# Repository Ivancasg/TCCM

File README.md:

# TCCM
Tarjeta de control para cámara de maduración

Desarrollado por alumnos del ITM (Instituto tecnológico de Mérida)

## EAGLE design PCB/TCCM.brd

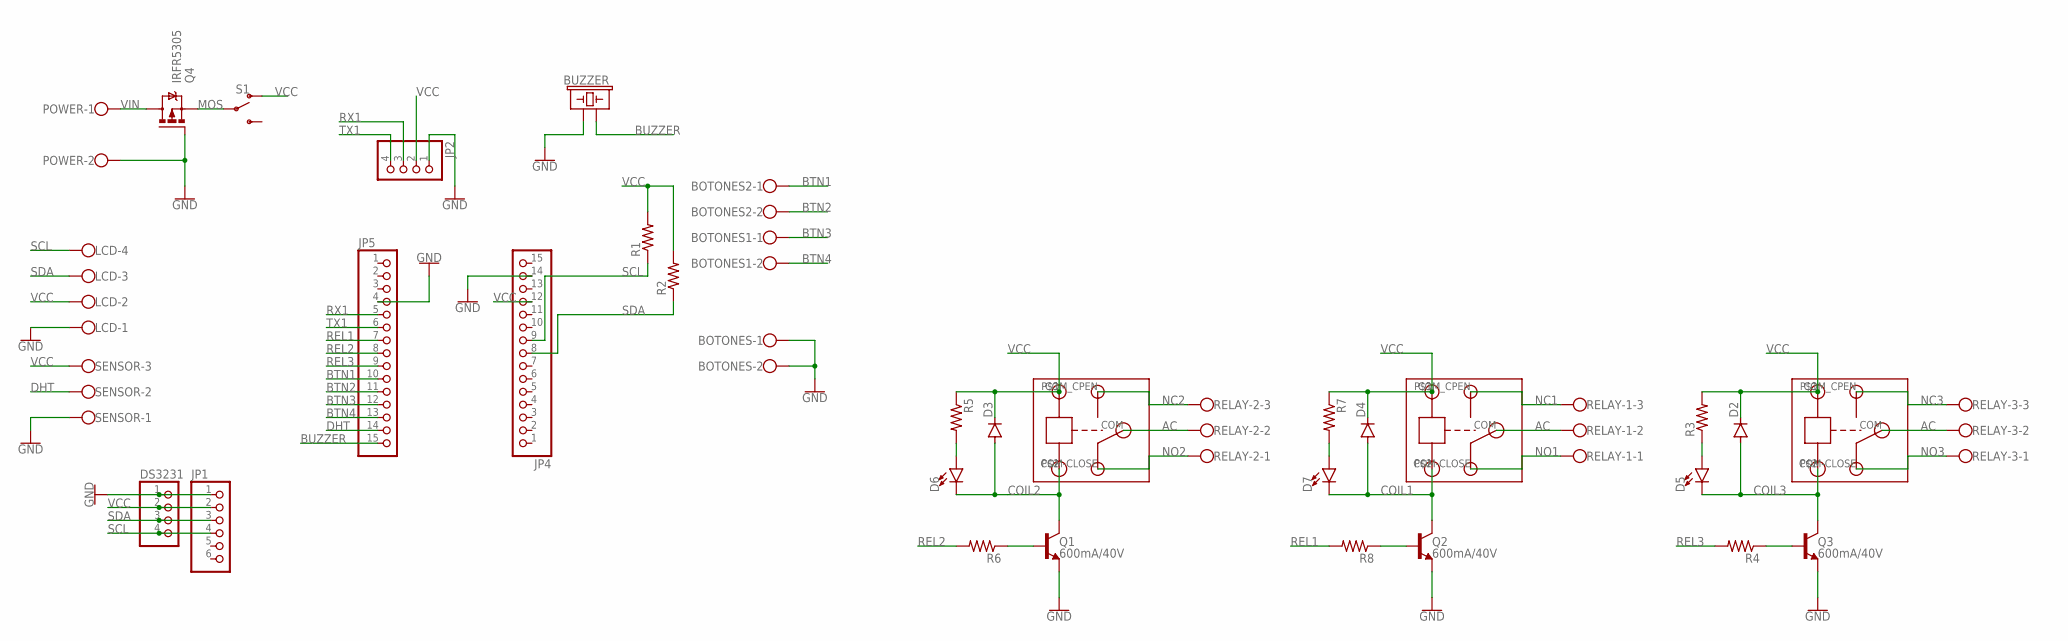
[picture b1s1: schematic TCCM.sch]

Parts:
BOTONES, BOTONES1, BOTONES2: W237-102
BUZZER: BUZZER-PTH; BUZZER-12MM
D2, D3, D4: 1N4148DO35-7; DO35-7
D5, D6, D7: LED3MM; LED_3MM
DS3231: PINHD-1X4; 1X04
JP1: PINHD-1X6; 1X06
JP2: PINHD-1X4; 1X04
JP4, JP5: PINHD-1X15; 1X15
LCD: W237-4
POWER: W237-102
Q1, Q2, Q3: 600mA/40V; TO-92
Q4: IRFR5305; D-PAK_TO252AA
R1, R2, R3, R4, R5, R6, R7, R8: R-US_0207/7; 0207/7
RELAY-1, RELAY-2, RELAY-3: W237-103
S1: SWITCH-SPDT-PTH-11.6X4.0MM; SWITCH_SPDT_PTH_11.6X4.0MM
SENSOR: W237-103
U$1, U$2, U$3: RELAY

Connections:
AC: RELAY-1.2, RELAY-2.2, RELAY-3.2, U$1.COM, U$2.COM, U$3.COM
BTN1: BOTONES2.1, JP5.10
BTN2: BOTONES2.2, JP5.11
BTN3: BOTONES1.1, JP5.12
BTN4: BOTONES1.2, JP5.13
BUZZER: BUZZER.+ (1), JP5.15
COIL1: D4.A, D7.K (C), Q2.1 (C), U$2.P$2 (GND)
COIL2: D3.A, D6.K (C), Q1.1 (C), U$1.P$2 (GND)
COIL3: D2.A, D5.K (C), Q3.1 (C), U$3.P$2 (GND)
DHT: JP5.14, SENSOR.2
GND: BOTONES.1, BOTONES.2, BUZZER.- (2), DS3231.1, JP1.1, JP2.1, JP4.14, JP5.4, LCD.1, POWER.2, Q1.3 (E), Q2.3 (E), Q3.3 (E), Q4.1 (G), SENSOR.1
LED1: D7.A, R7.2
LED2: D6.A, R5.2
LED3: D5.A, R3.1
MOS: Q4.3 (S), S1.2
unnamed: Q3.2 (B), R4.1
unnamed: Q2.2 (B), R8.1
unnamed: Q1.2 (B), R6.1
NC1: RELAY-1.3, U$2.COM_CPEN (COM-OPEN)
NC2: RELAY-2.3, U$1.COM_CPEN (COM-OPEN)
NC3: RELAY-3.3, U$3.COM_CPEN (COM-OPEN)
NO1: RELAY-1.1, U$2.COM-CLOSE
NO2: RELAY-2.1, U$1.COM-CLOSE
NO3: RELAY-3.1, U$3.COM-CLOSE
REL1: JP5.7, R8.2
REL2: JP5.8, R6.2
REL3: JP5.9, R4.2
RX1: JP2.3, JP5.5
SCL: DS3231.4, JP1.4, JP4.9, LCD.4, R1.1
SDA: DS3231.3, JP1.3, JP4.8, LCD.3, R2.1
TX1: JP2.4, JP5.6
VCC: D2.C, D3.C, D4.C, DS3231.2, JP1.2, JP2.2, JP4.12, LCD.2, R1.2, R2.2, R3.2, R5.1, R7.1, S1.1 (O), SENSOR.3, U$1.P$1 (IN), U$2.P$1 (IN), U$3.P$1 (IN)
VIN: POWER.1, Q4.4 (D)

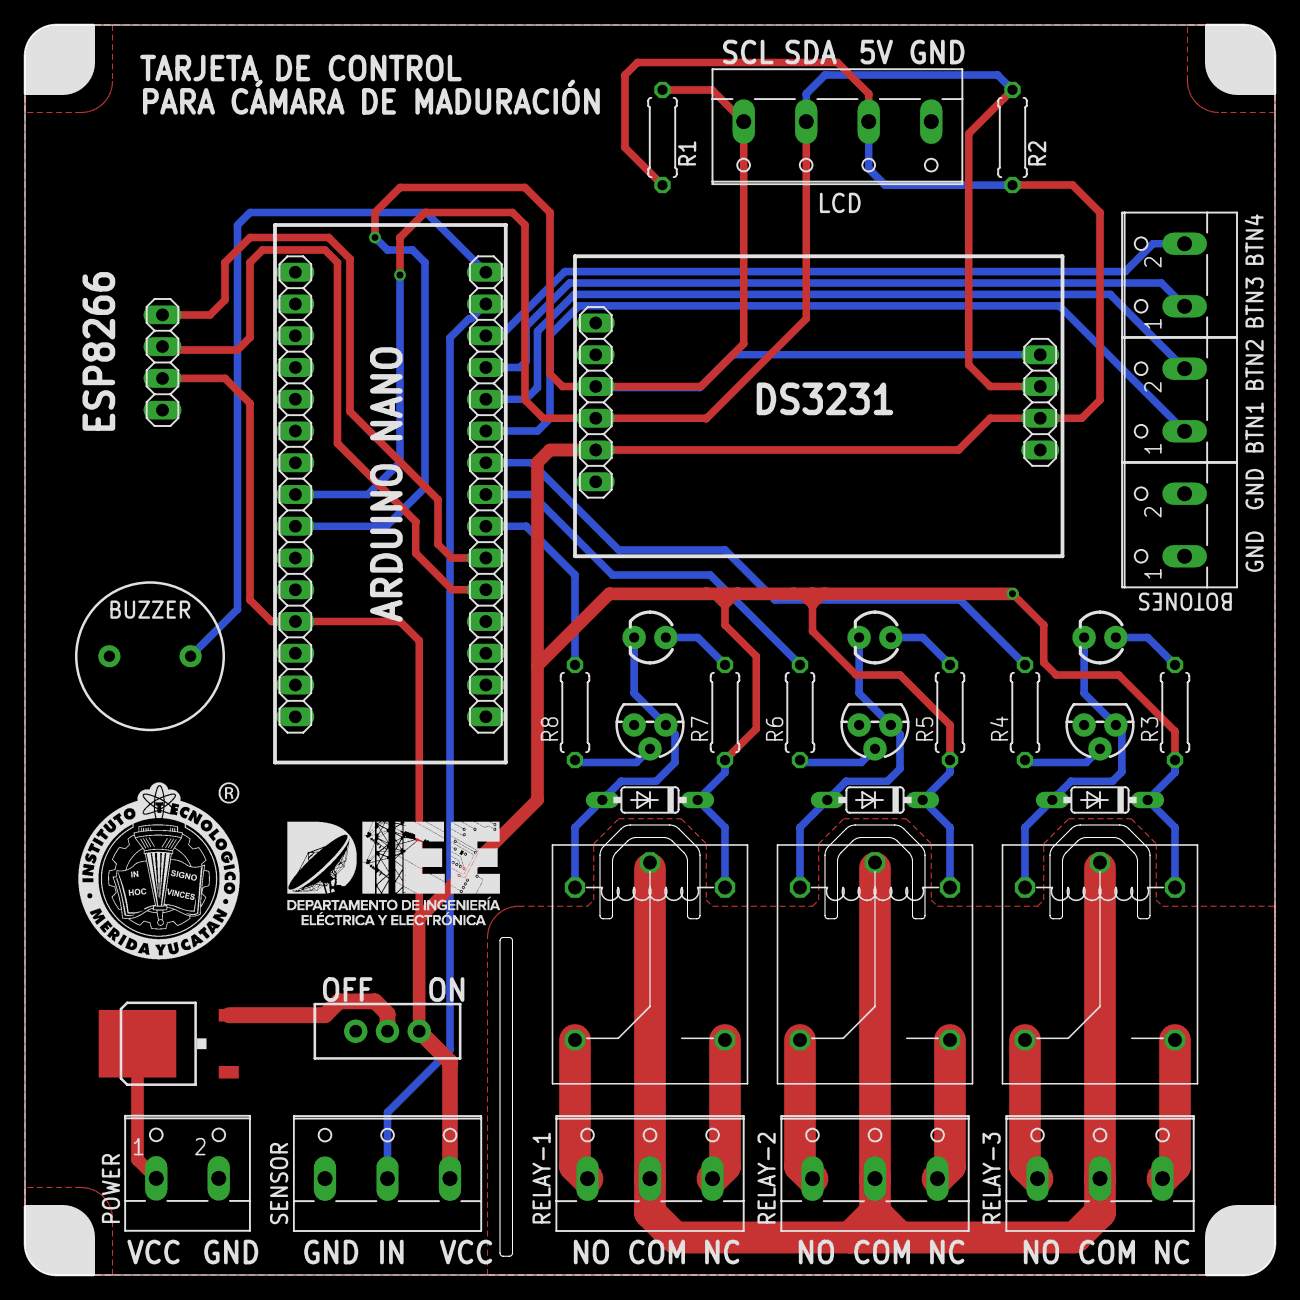
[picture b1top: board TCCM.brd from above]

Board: 2 copper layers, 100.0 x 100.0 mm, 37 parts (0 on the bottom side), 33 nets.

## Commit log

2019-09-16 Add PCB files
2019-09-16 Add code files
2019-09-16 Add libraries files
2019-09-16 Update libraries

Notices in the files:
parts and their libraries:
SparkFun-Electromechanical: Licensing: Creative Commons ShareAlike 4.0 International - https://creativecommons.org/licenses/by-sa/4.0
